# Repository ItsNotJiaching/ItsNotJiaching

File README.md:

## Hi there 👋
This repository is a collection of my past projects. You can check out a summary of my work (and an About Me) here: https://sites.google.com/view/jiaxingwang/projects

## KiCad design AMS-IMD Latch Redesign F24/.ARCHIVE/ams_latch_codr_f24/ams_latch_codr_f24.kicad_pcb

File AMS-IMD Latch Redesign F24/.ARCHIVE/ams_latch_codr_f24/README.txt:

AMS Latch PCB

Last updated 5/1/22

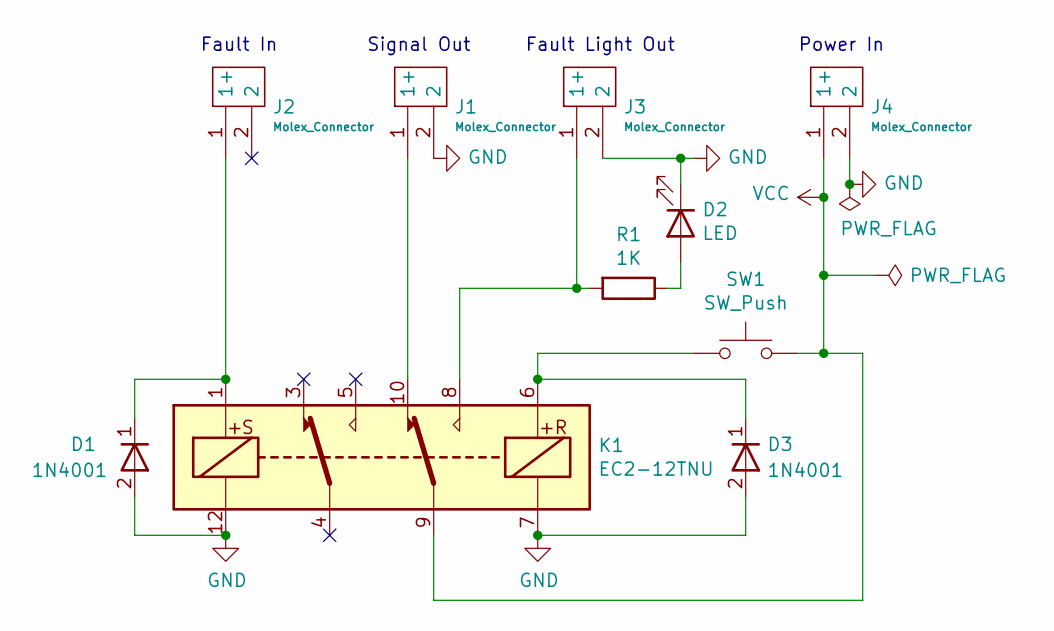
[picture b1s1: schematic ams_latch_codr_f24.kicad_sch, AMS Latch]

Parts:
D1, D3: 1N4001; D_DO-41_SOD81_P10.16mm_Horizontal_Motorsport
D2: LED; LED_D5.0mm_Motorsport
J1, J2, J3, J4: Molex_Connector; 39-28-8020_Motorsport; Manufacturer_Part_Number 39-28-8020; Mouser Part Number 538-39-28-8020
K1: EC2-12TNU; Relay_DPDT_Kemet_EC2_DoubleCoil_Motorsport
R1: 1K; R_Axial_DIN0207_L6.3mm_D2.5mm_P7.62mm_Horizontal_Motorsport
SW1: SW_Push; SW_PUSH_6mm_Motorsport

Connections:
GND: D1.2 (A), D2.1 (K), D3.2 (A), J1.2, J3.2, J4.2, K1.7, K1.12
unnamed: D1.1 (K), J2.1 (1+), K1.1
unnamed: D2.2 (A), R1.1
unnamed: D3.1 (K), K1.6, SW1.1
unnamed: J1.1 (1+), K1.10
unnamed: J3.1 (1+), K1.8, R1.2
VCC: J4.1 (1+), K1.9, SW1.2

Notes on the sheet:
Fault In
Fault Light Out
Power In
Signal Out

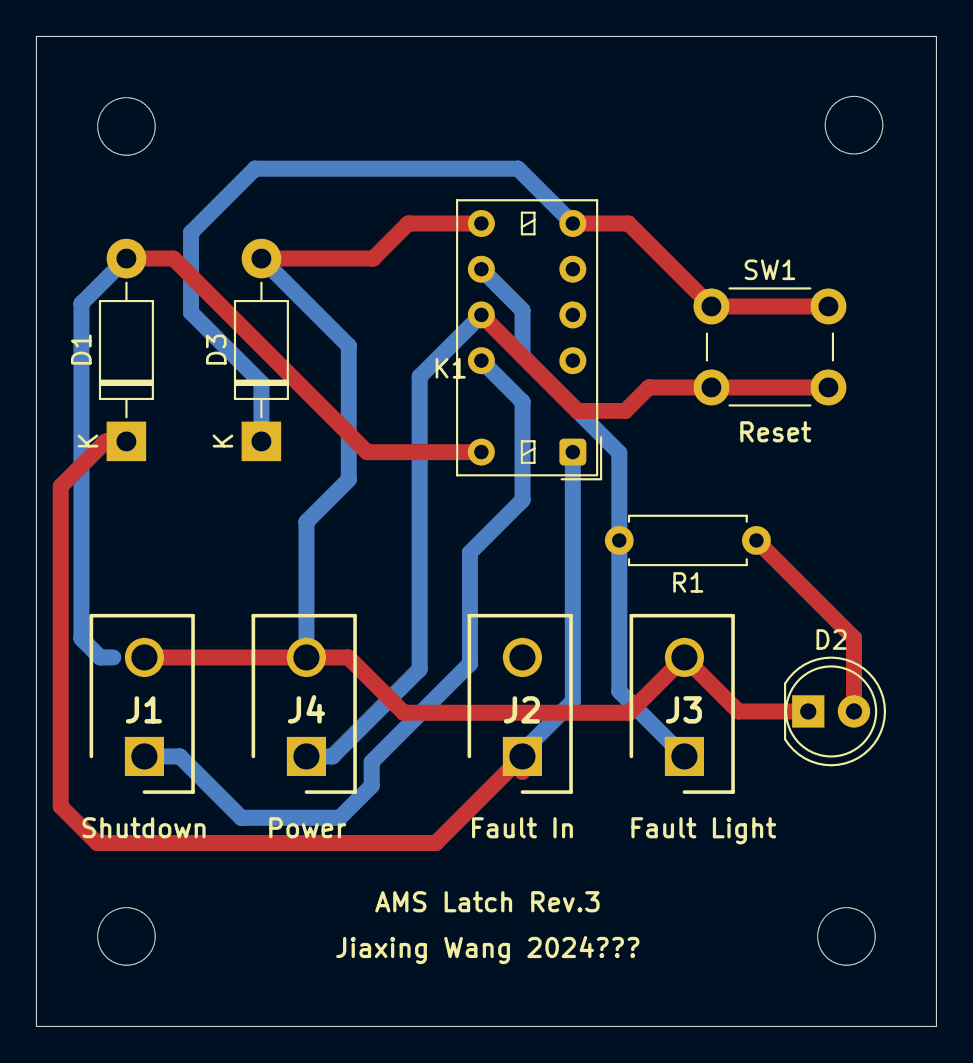
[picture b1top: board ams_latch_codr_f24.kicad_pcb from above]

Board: 2 copper layers, 50.0 x 55.0 mm, 10 parts (0 on the bottom side), 7 nets.

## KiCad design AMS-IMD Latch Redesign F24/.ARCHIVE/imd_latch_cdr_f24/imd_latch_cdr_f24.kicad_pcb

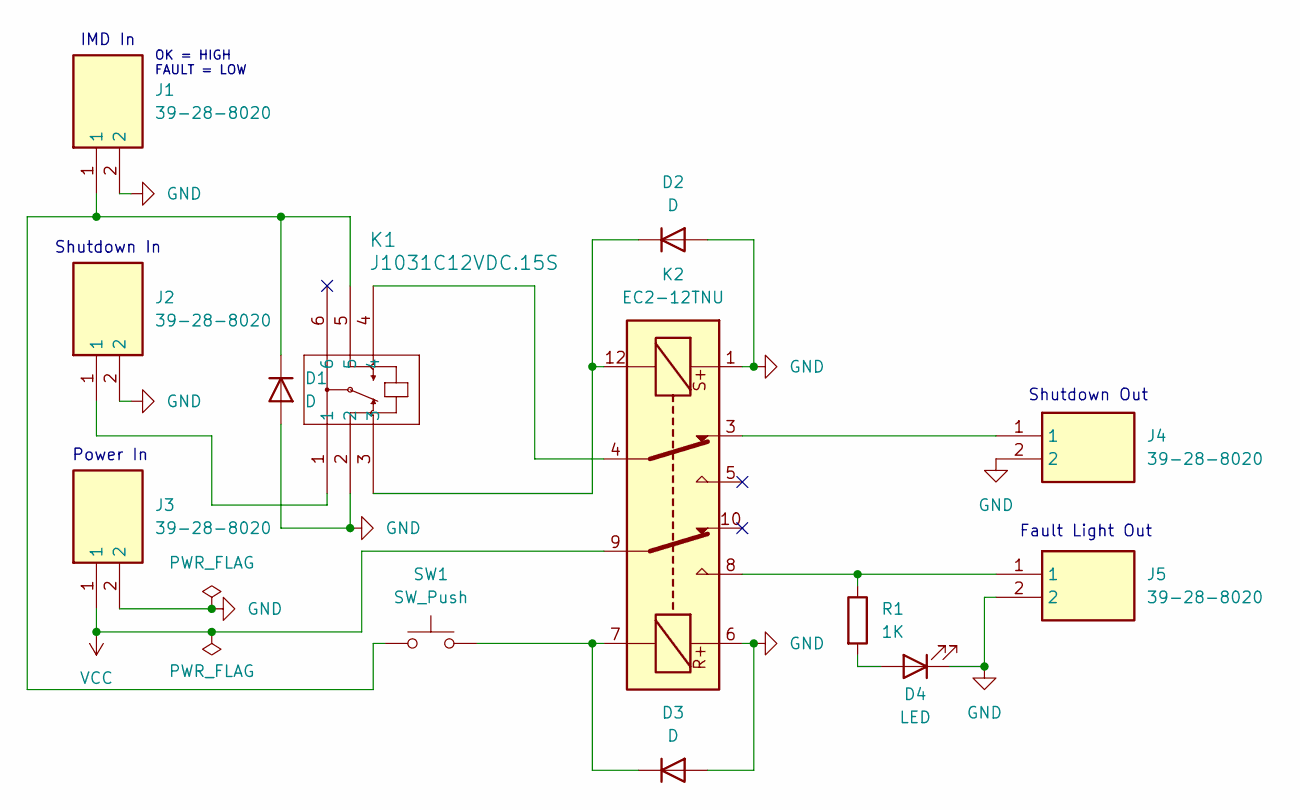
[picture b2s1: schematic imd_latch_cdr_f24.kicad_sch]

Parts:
D1, D2, D3: D; D_DO-41_SOD81_P10.16mm_Horizontal
D4: LED; LED_D5.0mm
J1, J2, J3, J4, J5: 39-28-8020; Mouser Part Number 538-39-28-8020
K1: J1031C12VDC.15S; J103_CRS
K2: EC2-12TNU; Relay_DPDT_Kemet_EC2_DoubleCoil
R1: 1K; R_Axial_DIN0207_L6.3mm_D2.5mm_P7.62mm_Horizontal
SW1: SW_Push; SW_PUSH_6mm

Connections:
GND: D1.2 (A), D2.2 (A), D3.2 (A), D4.1 (K), J1.2, J2.2, J3.2, J4.2, J5.2, K1.2, K2.1, K2.6
unnamed: D1.1 (K), J1.1, K1.5, SW1.1
unnamed: D2.1 (K), K1.3, K2.12
unnamed: D3.1 (K), K2.7, SW1.2
unnamed: D4.2 (A), R1.2
unnamed: J2.1, K1.1
unnamed: J4.1, K2.3
unnamed: J5.1, K2.8, R1.1
unnamed: K1.4, K2.4
VCC: J3.1, K2.9

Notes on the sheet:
IMD In
Fault Light Out
OK = HIGH FAULT = LOW
Shutdown In
Shutdown Out
Power In

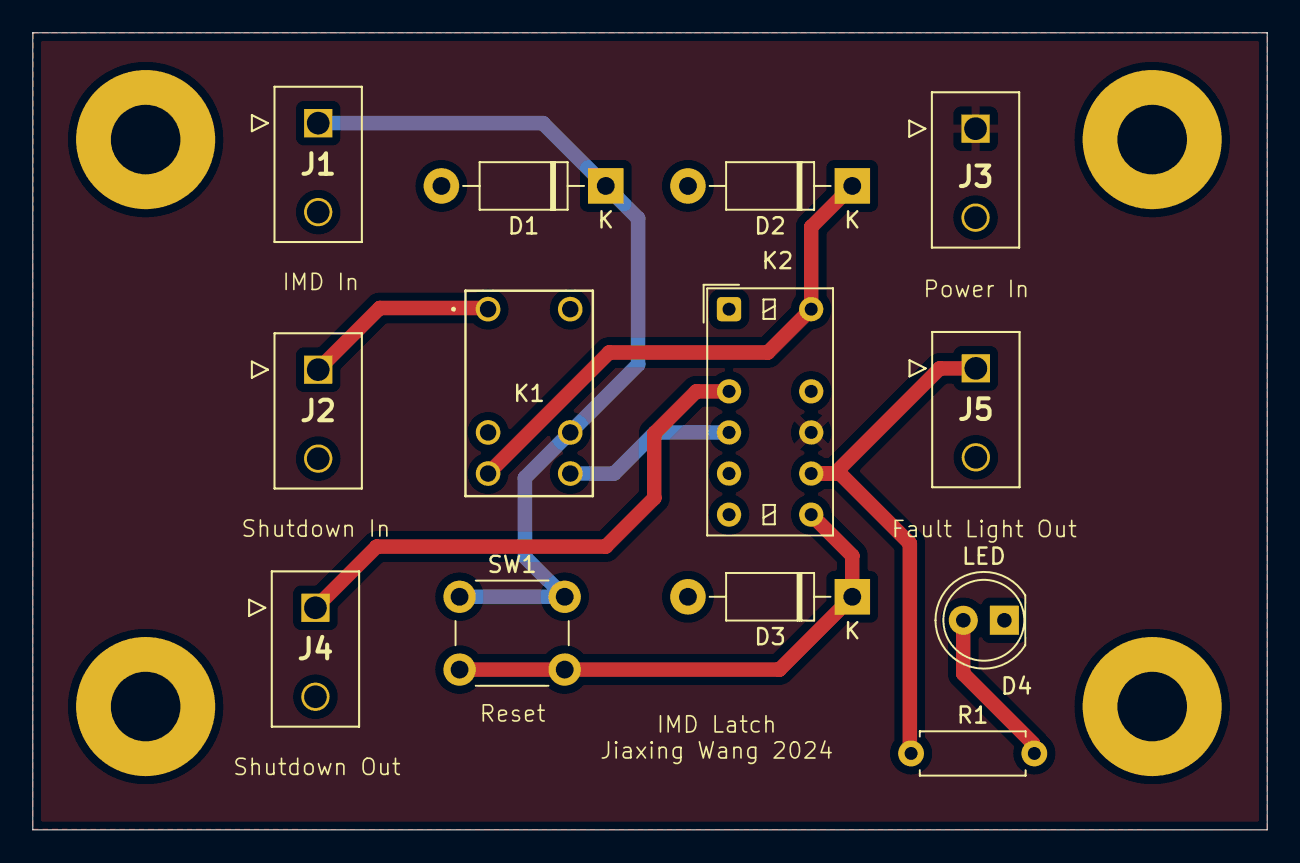
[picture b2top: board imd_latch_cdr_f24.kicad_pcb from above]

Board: 2 copper layers, 76.3 x 49.3 mm, 13 parts (0 on the bottom side), 10 nets.

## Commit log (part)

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2025-12-10 EK301 Folder
2026-03-01 Update README to add repository introduction
    Updated README to describe repository content and link to projects.
2026-03-01 Delete introduction from README
    Remove introductory section about past projects.
2026-03-01 Add Retro Doorbell Project
2026-03-01 Add AMS/IMD Latch
